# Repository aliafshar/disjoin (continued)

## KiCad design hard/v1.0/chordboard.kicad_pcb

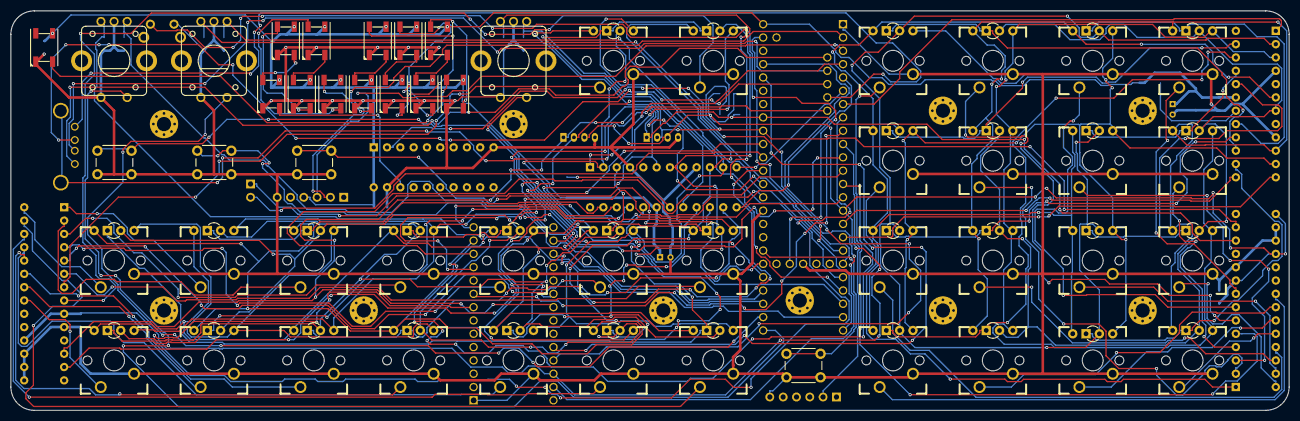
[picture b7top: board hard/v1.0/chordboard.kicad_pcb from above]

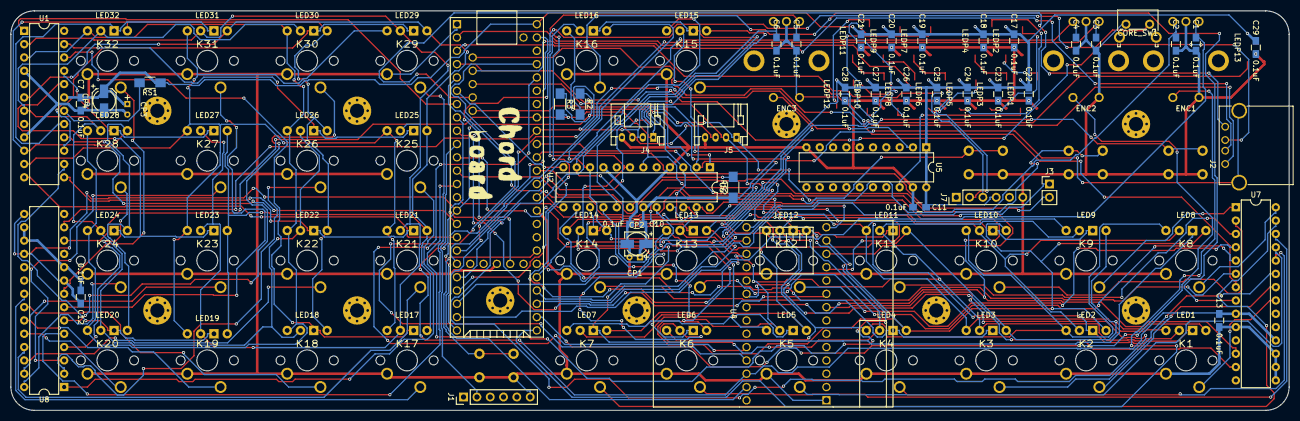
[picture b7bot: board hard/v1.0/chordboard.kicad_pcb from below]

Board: 2 copper layers, 243.8 x 76.2 mm, 141 parts (47 on the bottom side), 123 nets.

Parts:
C1, C2, C3, C4, C5, C6, C7, C10, C11, C12, C13, C17, C18, C19, C20, C21, C22, C23, C24, C25, C26, C27, C28, C29: 0.1uF; C_0805_HandSoldering
CORE_SW1: PGM; SW_Tactile_SPST_Angled_PTS645Vx58-2LFS
CP1, CP3: 10uF; CP_Radial_D4.0mm_P2.00mm
CP2, CP4: 10uF; c_elec_4x4.5
ENC1, ENC2, ENC3: ROTARY_ENCODER; Rotary_Encoder_BI_EN12-HS22AF30
J1, J7: CONN_01X06; Pin_Header_Straight_1x06_Pitch2.54mm
J2: USB_A
J3: CONN_01X02; Pin_Header_Straight_1x02_Pitch2.54mm
J4, J5: I2C; JST_PH_S4B-PH-K_04x2.00mm_Angled
K1, K2, K3, K4, K5, K6, K7, K8, K9, K10, K11, K12, K13, K14, K15, K16, K17, K18, K19, K20, K21, K22, K23, K24, K25, K26, K27, K28, K29, K30, K31, K32: KSW; CHERRY_PCB_100H
LED1, LED2, LED3, LED4, LED5, LED6, LED7, LED8, LED9, LED10, LED11, LED12, LED13, LED14, LED15, LED16, LED17, LED18, LED19, LED20, LED21, LED22, LED23, LED24, LED25, LED26, LED27, LED28, LED29, LED30, LED31, LED32: LED_ARGB; LED_D3.0mm-4
LEDP1, LEDP2, LEDP3, LEDP4, LEDP5, LEDP6, LEDP7, LEDP8, LEDP9, LEDP10, LEDP11, LEDP12, LEDP13: WS2812B; LED_WS2812B-PLCC4-HandSolder
MK1, MK2, MK3, MK4, MK5, MK6, MK7, MK8, MK9, MK10: Mounting_Hole
R2, R3: 4.7K; R_1206_HandSoldering
RS1, RS2: 10K; R_1206_HandSoldering
SW1, SW2, SW3, SW4: KSW; SW_PUSH_6mm
SYM1: SYM_Arrow45_Large; CHORDBOARD_LOGO
U1, U6: MAX7219; DIP-24_W7.62mm
U2: Teensy3.6; Teensy35_36_external_pins
U4: Teensy_Audio_Board
U5: 74HC245; DIP-20_W7.62mm
U7, U8: MCP23017; DIP-28_W7.62mm

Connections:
+3V3: C12.1, C13.1, J4.3, J5.3, R2.1, R3.1, U2.15, U4.26, U7.9, U7.18, U8.9, U8.15, U8.18
+5V: C7.1, C10.1, C11.1, C17.1, C18.1, C19.1, C20.1, C21.1, C22.1, C23.1, C24.1, C25.1, C26.1, C27.1, C28.1, C29.1, CP1.1, CP2.1, CP3.1, CP4.1, J7.4, LEDP1.1, LEDP2.1, LEDP3.1, LEDP4.1, LEDP5.1, LEDP6.1, LEDP7.1, LEDP8.1, LEDP9.1, LEDP10.1, LEDP11.1, LEDP12.1, LEDP13.1, RS1.1, RS2.1, U1.19, U2.53, U5.1, U5.20, U6.19
/AUMEM_CS: U2.8, U4.8
/AUSD_CS: U2.12, U4.12
/AU_BCLK: U2.11, U4.11
/AU_LRCLK: U2.50, U4.25
/AU_MCLK: U2.13, U4.13
/AU_RX: U2.40, U4.15
/AU_TX: U2.49, U4.24
/AU_VOL: U2.42, U4.17
/CORE_PGM: CORE_SW1.2, U2.28
/LED2_CLK: U1.13, U2.16
/LED2_DIN: U1.1, U2.7
/LED2_LOAD: U1.12, U2.17
/LED_CLK: U2.5, U6.13
/LED_DIN: U2.4, U6.1
/LED_LOAD: U2.6, U6.12
/MISO: U2.14, U4.14
/MOSI: U2.9, U4.9
/PIXEL_DIN: U2.24, U5.2
/RE1_A: C2.1, ENC1.A, U2.22
/RE1_B: C1.1, ENC1.B, U2.23
/RE1_SW: ENC1.SW1, U2.30
/RE2_A: C4.1, ENC2.A, U2.18
/RE2_B: C3.1, ENC2.B, U2.19
/RE2_SW: ENC2.SW1, U2.31
/RE3_A: C6.1, ENC3.A, U2.20
/RE3_B: C5.1, ENC3.B, U2.21
/RE3_SW: ENC3.SW1, U2.32
/SCK: U2.41, U4.16
/SCL: J4.1, J5.1, R3.2, U2.46, U4.21, U7.12, U8.12
/SDA: J4.2, J5.2, R2.2, U2.45, U4.20, U7.13, U8.13
/U1_RX: J7.2, U2.2
/U1_TX: J7.3, U2.3
/U3_TX: J1.2, U2.10
/USBH_DM: J2.2, U2.59
/USBH_DP: J2.3, U2.60
/WIFI_PGM: J3.1, U2.44
/WIFI_RST: J3.2, U2.43
/X0: LED1.1, LED2.1, U6.22
/X1: LED3.1, LED4.1, U6.14
/X2: LED5.1, LED6.1, U6.16
/X3: LED7.1, LED8.1, U6.20
/X4: LED9.1, LED10.1, U6.23
/X5: LED11.1, LED12.1, U6.21
/X6: LED13.1, LED14.1, U6.15
/X7: LED15.1, LED16.1, U6.17
/X20: LED17.1, LED18.1, U1.22
/X21: LED19.1, LED20.1, U1.14
/X22: LED21.1, LED22.1, U1.16
/X23: LED23.1, LED24.1, U1.20
/X24: LED25.1, LED26.1, U1.23
/X25: LED27.1, LED28.1, U1.21
/X26: LED29.1, LED30.1, U1.15
/X27: LED31.1, LED32.1, U1.17
/Y0: LED1.4, LED3.4, LED5.4, LED7.4, LED9.4, LED11.4, LED13.4, LED15.4, U6.2
/Y1: LED1.3, LED3.3, LED5.3, LED7.3, LED9.3, LED11.3, LED13.3, LED15.3, U6.11
/Y2: LED1.2, LED3.2, LED5.2, LED7.2, LED9.2, LED11.2, LED13.2, LED15.2, U6.6
/Y3: LED2.4, LED4.4, LED6.4, LED8.4, LED10.4, LED12.4, LED14.4, LED16.4, U6.7
/Y4: LED2.3, LED4.3, LED6.3, LED8.3, LED10.3, LED12.3, LED14.3, LED16.3, U6.3
/Y5: LED2.2, LED4.2, LED6.2, LED8.2, LED10.2, LED12.2, LED14.2, LED16.2, U6.10
/Y20: LED17.4, LED19.4, LED21.4, LED23.4, LED25.4, LED27.4, LED29.4, LED31.4, U1.2
/Y21: LED17.3, LED19.3, LED21.3, LED23.3, LED25.3, LED27.3, LED29.3, LED31.3, U1.11
/Y22: LED17.2, LED19.2, LED21.2, LED23.2, LED25.2, LED27.2, LED29.2, LED31.2, U1.6
/Y23: LED18.4, LED20.4, LED22.4, LED24.4, LED26.4, LED28.4, LED30.4, LED32.4, U1.7
/Y24: LED18.3, LED20.3, LED22.3, LED24.3, LED26.3, LED28.3, LED30.3, LED32.3, U1.3
/Y25: LED18.2, LED20.2, LED22.2, LED24.2, LED26.2, LED28.2, LED30.2, LED32.2, U1.10
GND: C1.2, C2.2, C3.2, C4.2, C5.2, C6.2, C7.2, C10.2, C11.2, C12.2, C13.2, C17.2, C18.2, C19.2, C20.2, C21.2, C22.2, C23.2, C24.2, C25.2, C26.2, C27.2, C28.2, C29.2, CORE_SW1.1, CP1.2, CP2.2, CP3.2, CP4.2, ENC1.C, ENC1.SW2, ENC2.C, ENC2.SW2, ENC3.C, ENC3.SW2, J1.6, J4.4, J5.4, J7.6, K1.2, K2.2, K3.2, K4.2, K5.2, K6.2, K7.2, K8.2, K9.2, K10.2, K11.2, K12.2, K13.2, K14.2, K15.2, K16.2, K17.2, K18.2, K19.2, K20.2, K21.2, K22.2, K23.2, K24.2, K25.2, K26.2, K27.2, K28.2, K29.2, K30.2, K31.2, K32.2, LEDP1.3, LEDP2.3, LEDP3.3, LEDP4.3, LEDP5.3, LEDP6.3, LEDP7.3, LEDP8.3, LEDP9.3, LEDP10.3, LEDP11.3, LEDP12.3, LEDP13.3, SW1.2, SW2.2, SW3.2, SW4.2, U1.4, U1.9, U2.1, U2.27, U2.39, U4.1, U5.10, U5.19, U6.4, U6.9, U7.10, U7.15, U7.16, U7.17, U8.10, U8.16, U8.17
GNDA: U2.52, U4.27
unnamed: J2.1, U2.58
unnamed: J2.4, U2.61
unnamed: J2.5, U2.62
unnamed: K1.1, U7.21
unnamed: K2.1, U7.22
unnamed: K3.1, U7.23
unnamed: K4.1, U7.24
unnamed: K5.1, U7.25
unnamed: K6.1, U7.26
unnamed: K7.1, U7.27
unnamed: K8.1, U7.28
unnamed: K9.1, U7.1
unnamed: K10.1, U7.2
unnamed: K11.1, U7.3
unnamed: K12.1, U7.4
unnamed: K13.1, U7.5
unnamed: K14.1, U7.6
unnamed: K15.1, U7.7
unnamed: K16.1, U7.8
unnamed: K17.1, U8.21
unnamed: K18.1, U8.22
unnamed: K19.1, U8.23
unnamed: K20.1, U8.24
unnamed: K21.1, U8.25
unnamed: K22.1, U8.26
unnamed: K23.1, U8.27
unnamed: K24.1, U8.28
unnamed: K25.1, U8.1
unnamed: K26.1, U8.2
unnamed: K27.1, U8.3
unnamed: K28.1, U8.4
unnamed: K29.1, U8.5
unnamed: K30.1, U8.6
unnamed: K31.1, U8.7
unnamed: K32.1, U8.8
unnamed: LEDP1.2, LEDP2.4
unnamed: LEDP1.4, U5.18
unnamed: LEDP2.2, LEDP3.4
unnamed: LEDP3.2, LEDP4.4
unnamed: LEDP4.2, LEDP5.4
unnamed: LEDP5.2, LEDP6.4
unnamed: LEDP6.2, LEDP7.4
unnamed: LEDP7.2, LEDP8.4
unnamed: LEDP8.2, LEDP9.4
unnamed: LEDP10.2, LEDP11.4
unnamed: LEDP9.2, LEDP10.4
unnamed: LEDP11.2, LEDP12.4
unnamed: LEDP12.2, LEDP13.4
unnamed: RS1.2, U1.18
unnamed: RS2.2, U6.18
unnamed: SW1.1, U2.33
unnamed: SW2.1, U2.34
unnamed: SW3.1, U2.35
unnamed: SW4.1, U2.36

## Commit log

2019-02-11 initial import
